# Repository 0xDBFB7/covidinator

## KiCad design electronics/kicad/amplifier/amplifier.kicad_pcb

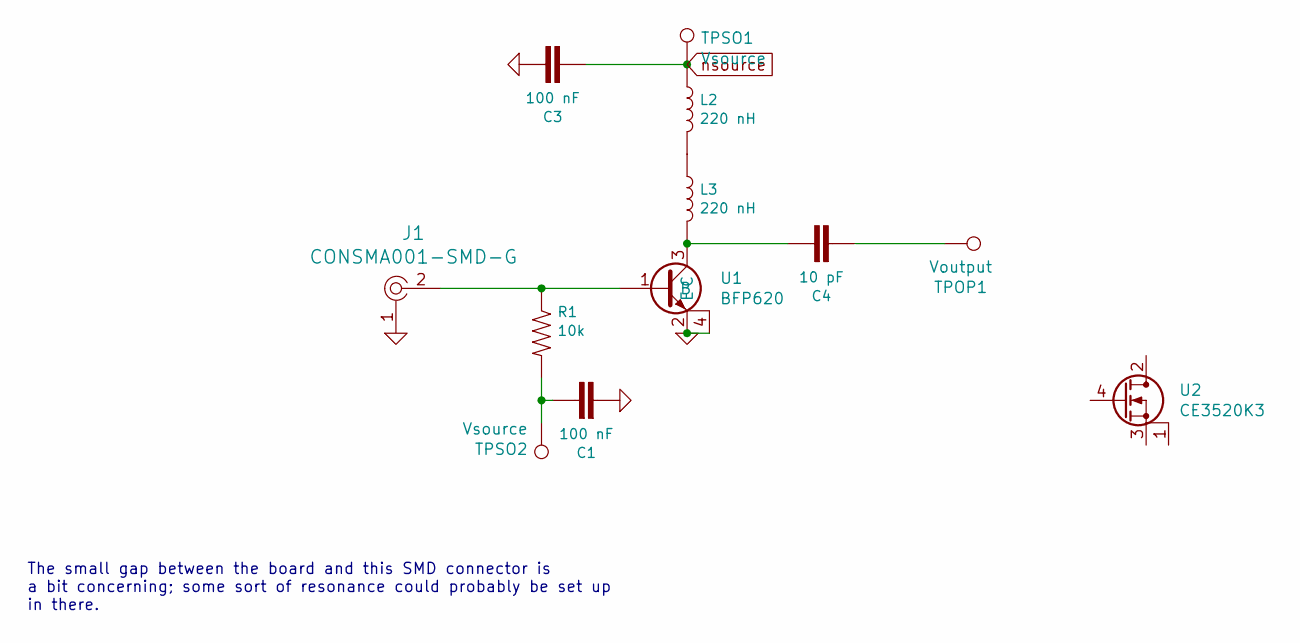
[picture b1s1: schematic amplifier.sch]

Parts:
C1, C3: 100 nF; 0603
C4: 10 pF; C_0402_1005Metric
J1: CONSMA001-SMD-G; RF_SMA_Receptical_Vertical_CONSMA001-SMD-G; MPN CONSMA001-SMD-G; Digi-Key_PN CONSMA001-SMD-G-ND
L2, L3: 220 nH; R_0402_1005Metric
R1: 10k; 0402
TPOP1: Voutput; TestPoint_Pad_1.5x1.5mm
TPSO1, TPSO2: Vsource; TestPoint_Pad_2.0x2.0mm
U1: BFP620; SOT-343_SC-70-4
U2: CE3520K3; 4-Micro-X

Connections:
GND: C1.2, C3.1, J1.1, U1.2 (E), U1.4
unnamed: C1.1, R1.2, TPSO2.1
unnamed: C4.1, L3.2, U1.3 (C)
unnamed: C4.2, TPOP1.1
unnamed: J1.2, R1.1, U1.1 (B)
unnamed: L2.2, L3.1
nsource: C3.2, L2.1, TPSO1.1

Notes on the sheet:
The small gap between the board and this SMD connector is a bit concerning; some sort of resonance could probably be set up in there.

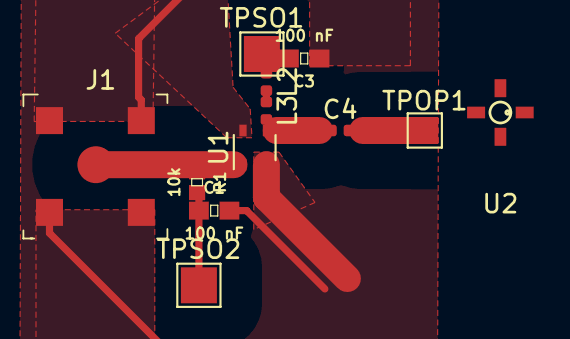
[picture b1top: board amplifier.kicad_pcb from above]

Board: 2 copper layers, 12 parts (0 on the bottom side), 7 nets.

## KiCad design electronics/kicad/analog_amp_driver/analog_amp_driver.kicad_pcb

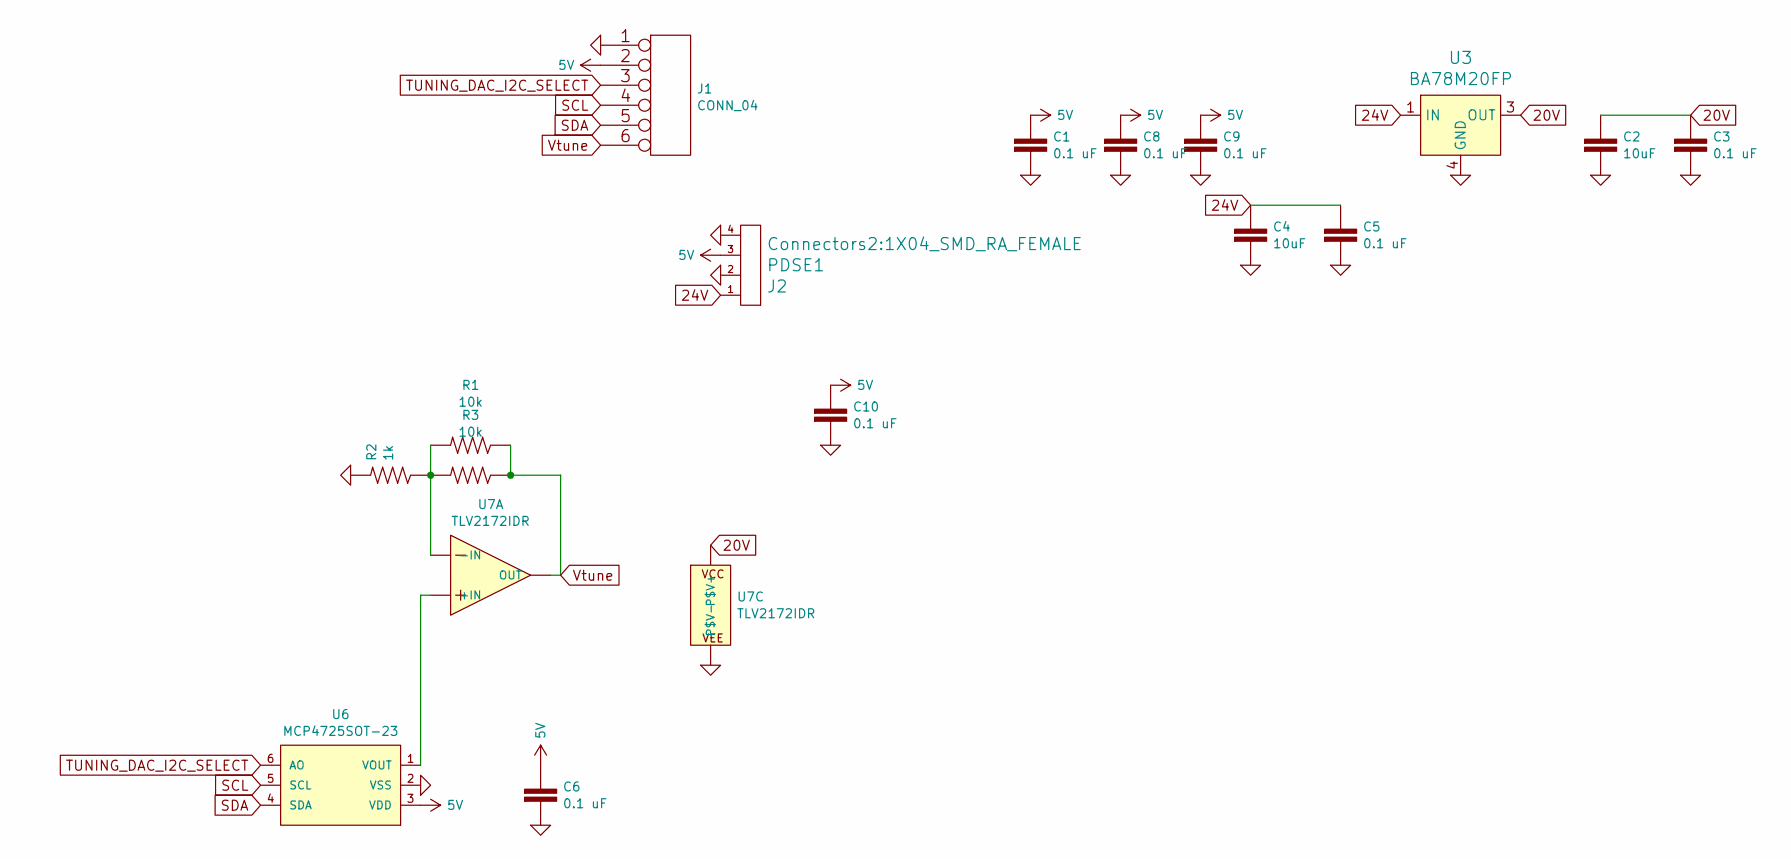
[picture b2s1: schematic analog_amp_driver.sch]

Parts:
C1, C3, C5, C6, C8, C9, C10: 0.1 uF; 0603
C2, C4: 10uF; 1206
J1: CONN_04; 1X06-SMD-FEMALE
J2: PDSE1; 1X04_SMD_RA_FEMALE
R1, R3: 10k; R_0603_1608Metric
R2: 1k; R_0603_1608Metric
U3: BA78M20FP; TO-252-3; MPN MC7805BDTRKG; Digi-Key_PN MC7805BDTRKGOSCT-ND
U6: MCP4725SOT-23; SOT23-6
U7: TLV2172IDR; SOIC-8_3.9x4.9mm_P1.27mm

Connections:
5V: C1.1, C6.1, C8.1, C9.1, C10.1, J1.2, J2.3, U6.3 (VDD)
20V: C2.1, C3.1, U3.3 (OUT), U7.8 (P$V+)
24V: C4.1, C5.1, J2.1, U3.1 (IN)
GND: C1.2, C2.2, C3.2, C4.2, C5.2, C6.2, C8.2, C9.2, C10.2, J1.1, J2.2, J2.4, R2.2, U3.4 (GND), U6.2 (VSS), U7.4 (P$V-)
unnamed: R1.2, R2.1, R3.2, U7.2 (-IN)
unnamed: U6.1 (VOUT), U7.3 (+IN)
SCL: J1.4, U6.5 (SCL)
SDA: J1.5, U6.4 (SDA)
TUNING_DAC_I2C_SELECT: J1.3, U6.6 (AO)
Vtune: J1.6, R1.1, R3.1, U7.1 (OUT)

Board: 2 copper layers, 17 parts (0 on the bottom side), 10 nets, no tracks yet.

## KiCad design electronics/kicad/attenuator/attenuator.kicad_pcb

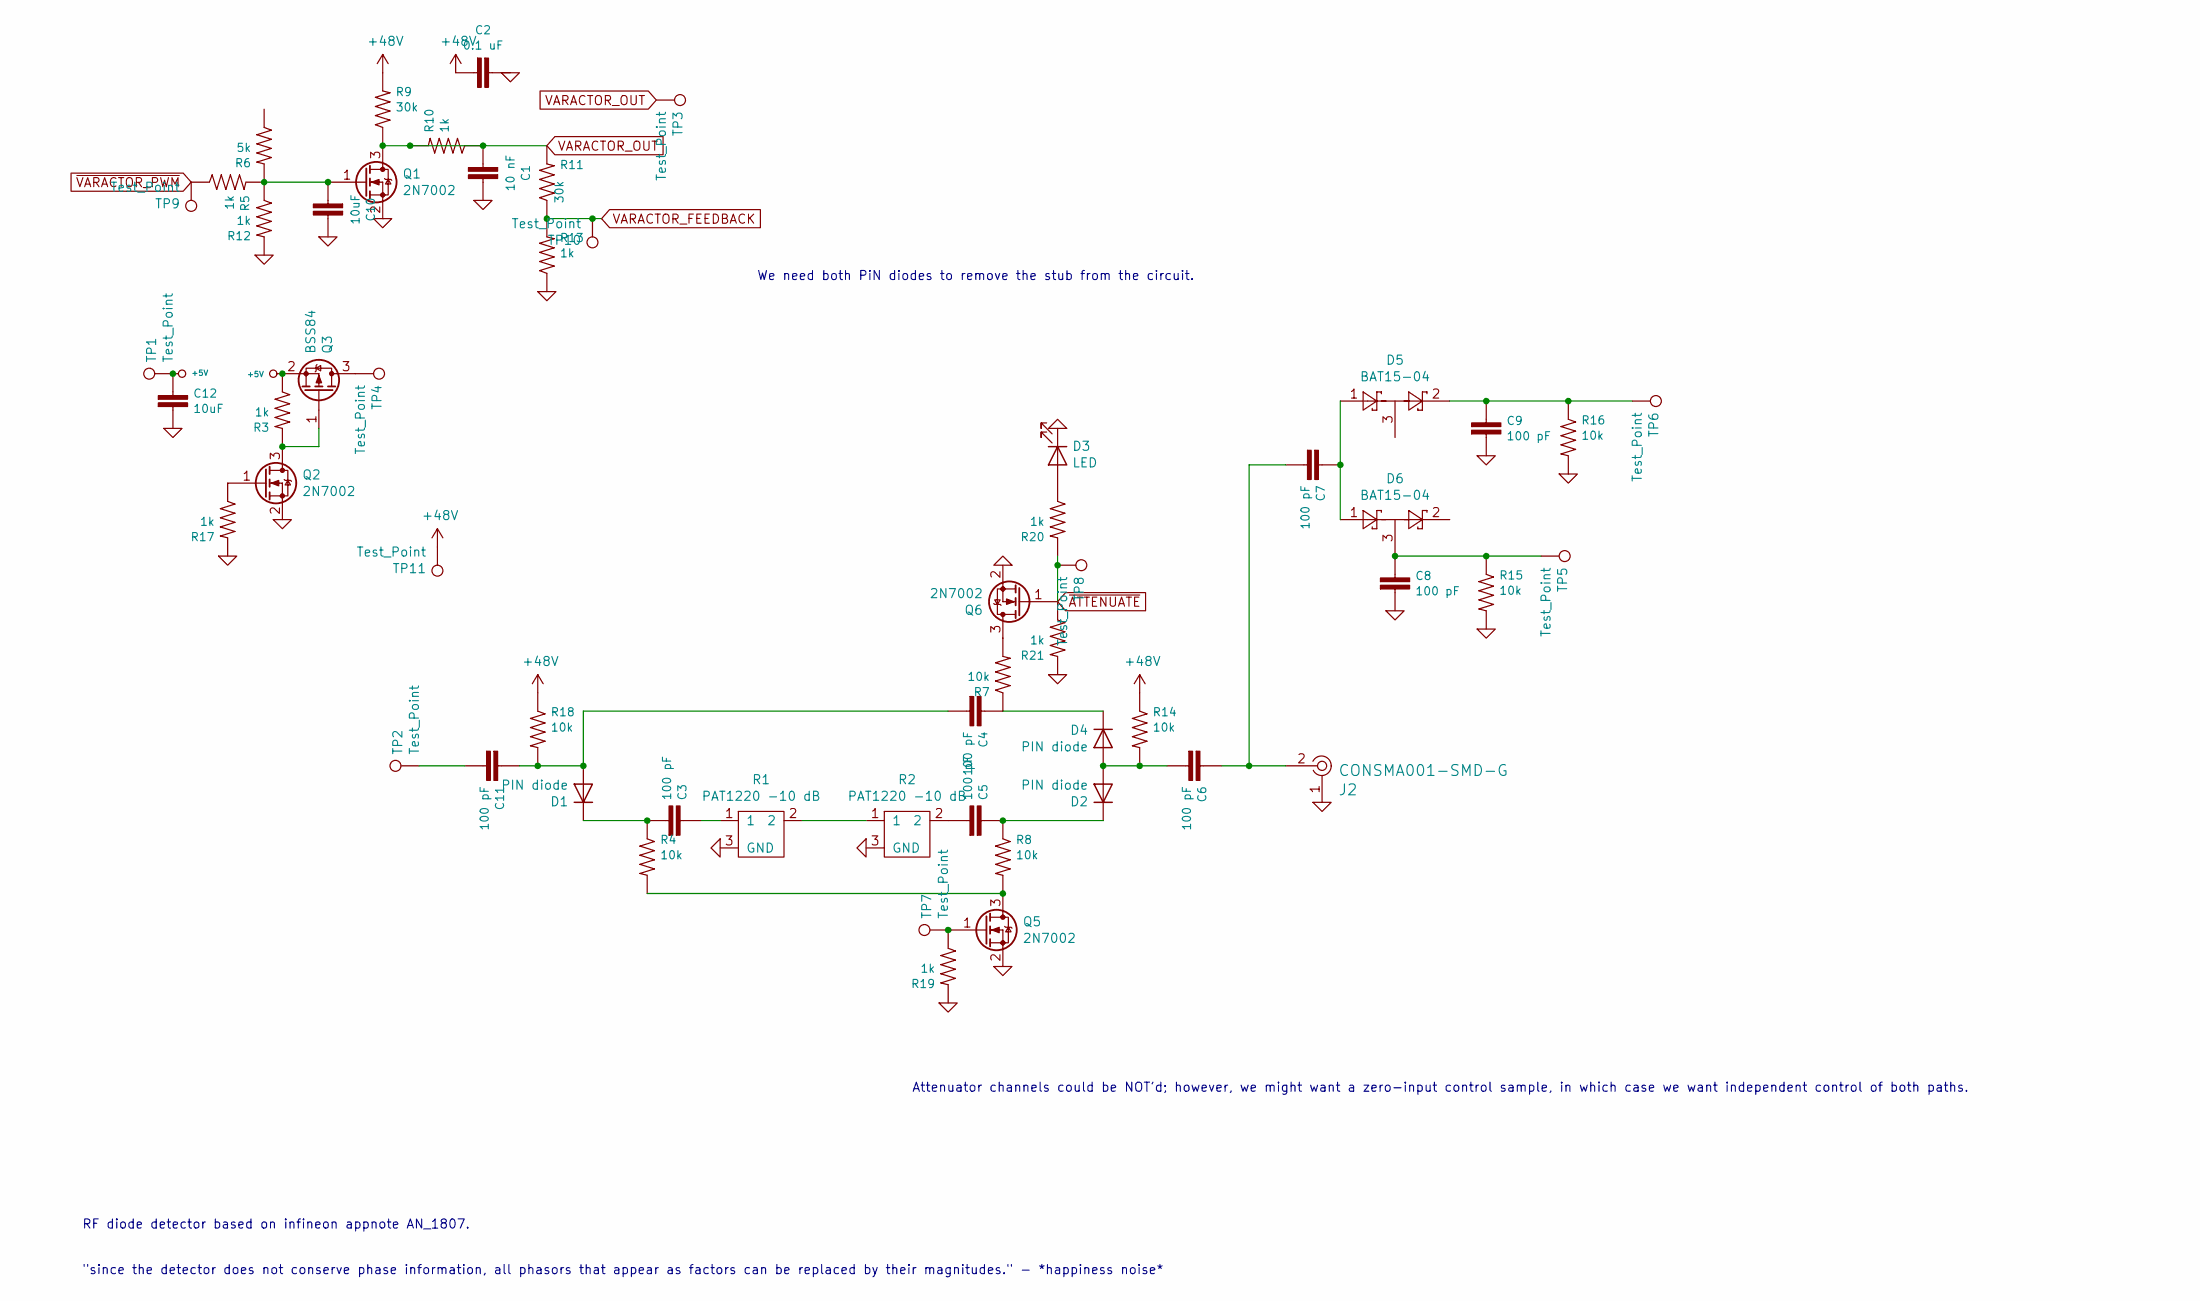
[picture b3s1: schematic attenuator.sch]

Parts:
C1: 10 nF; 0603
C2: 0.1 uF; 0603
C3, C4, C5, C6, C7, C8, C9, C11: 100 pF; 0402
C10: 10uF; 0603
C12: 10uF; 1206
D1, D2, D4: PIN diode; D_SOD-523
D3: LED; LED_0603_1608Metric
D5, D6: BAT15-04; SOT-23
J2: CONSMA001-SMD-G; RF_SMA_Receptical_Vertical_CONSMA001-SMD-G; MPN CONSMA001-SMD-G; Digi-Key_PN CONSMA001-SMD-G-ND
Q1, Q2, Q5, Q6: 2N7002; SOT-23
Q3: BSS84; SOT-23
R1, R2: PAT1220 -10 dB; PAT1220
R3, R5, R10, R12, R13, R17, R19, R20, R21: 1k; R_0603_1608Metric
R4, R7, R8, R14, R15, R16, R18: 10k; 0402
R6: 5k; R_0603_1608Metric
R9, R11: 30k; R_0603_1608Metric
TP1, TP3, TP4, TP5, TP6, TP9, TP10: Test_Point; TestPoint_Pad_2.0x2.0mm
TP2, TP7, TP8, TP11: Test_Point; TestPoint_Pad_1.5x1.5mm

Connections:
+5V: C12.1, Q3.2 (S), R3.1, TP1.1
+48V: C2.2, R9.2, R14.1, R18.1, TP11.1
GND: C1.1, C2.1, C8.2, C9.2, C10.1, C12.2, D3.1 (K), J2.1, Q1.2 (S), Q2.2 (S), Q5.2 (S), Q6.2 (S), R1.3 (GND), R2.3 (GND), R12.2, R13.1, R15.2, R16.2, R17.2, R19.2, R21.2
unnamed: C3.1, R1.1
unnamed: C3.2, D1.1 (K), R4.1
unnamed: C4.1, D4.1 (K), R7.1
unnamed: C5.1, D2.1 (K), R8.1
unnamed: C5.2, R2.2
unnamed: C6.1, C7.2, J2.2
unnamed: C6.2, D2.2 (A), D4.2 (A), R14.2
unnamed: C7.1, D5.1, D6.1
unnamed: C8.1, D6.3, R15.1, TP5.1
unnamed: C9.1, D5.2, R16.1, TP6.1
unnamed: C10.2, Q1.1 (G), R5.2, R6.2, R12.1
unnamed: C4.2, C11.1, D1.2 (A), R18.2
unnamed: C11.2, TP2.1
unnamed: D3.2 (A), R20.1
unnamed: Q2.1 (G), R17.1
unnamed: Q2.3 (D), Q3.1 (G), R3.2
unnamed: Q3.3 (D), TP4.1
unnamed: Q5.1 (G), R19.1, TP7.1
unnamed: Q5.3 (D), R4.2, R8.2
unnamed: Q6.3 (D), R7.2
unnamed: R1.2, R2.1
VARACTOR_FEEDBACK: R11.1, R13.2, TP10.1
VARACTOR_OUT: C1.2, Q1.3 (D), R9.1, R10.1, R10.2, R11.2, TP3.1
~ATTENUATE: Q6.1 (G), R20.2, R21.1, TP8.1
~VARACTOR_PWM: R5.1, TP9.1

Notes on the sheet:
"since the detector does not conserve phase information, all phasors that appear as factors can be replaced by their magnitudes." - *happiness noise*
RF diode detector based on infineon appnote AN_1807.
Attenuator channels could be NOT'd; however, we might want a zero-input control sample, in which case we want independent control of both paths.
We need both PiN diodes to remove the stub from the circuit.

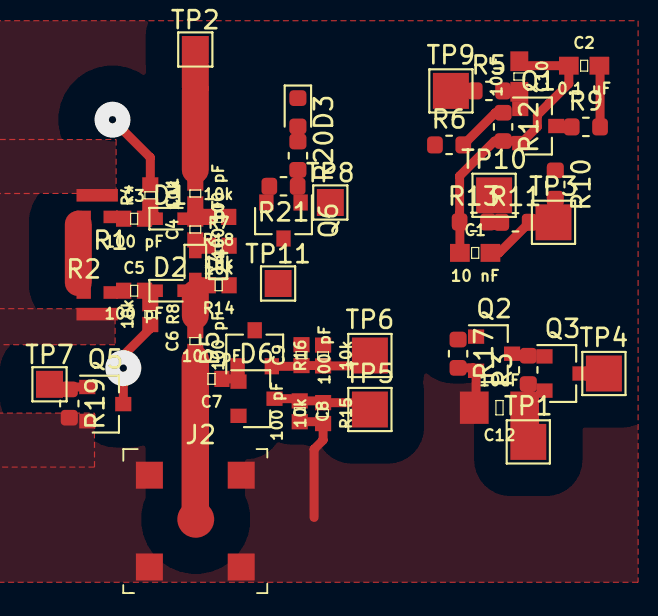
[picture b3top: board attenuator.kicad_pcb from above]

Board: 2 copper layers, 56 parts (0 on the bottom side), 28 nets.

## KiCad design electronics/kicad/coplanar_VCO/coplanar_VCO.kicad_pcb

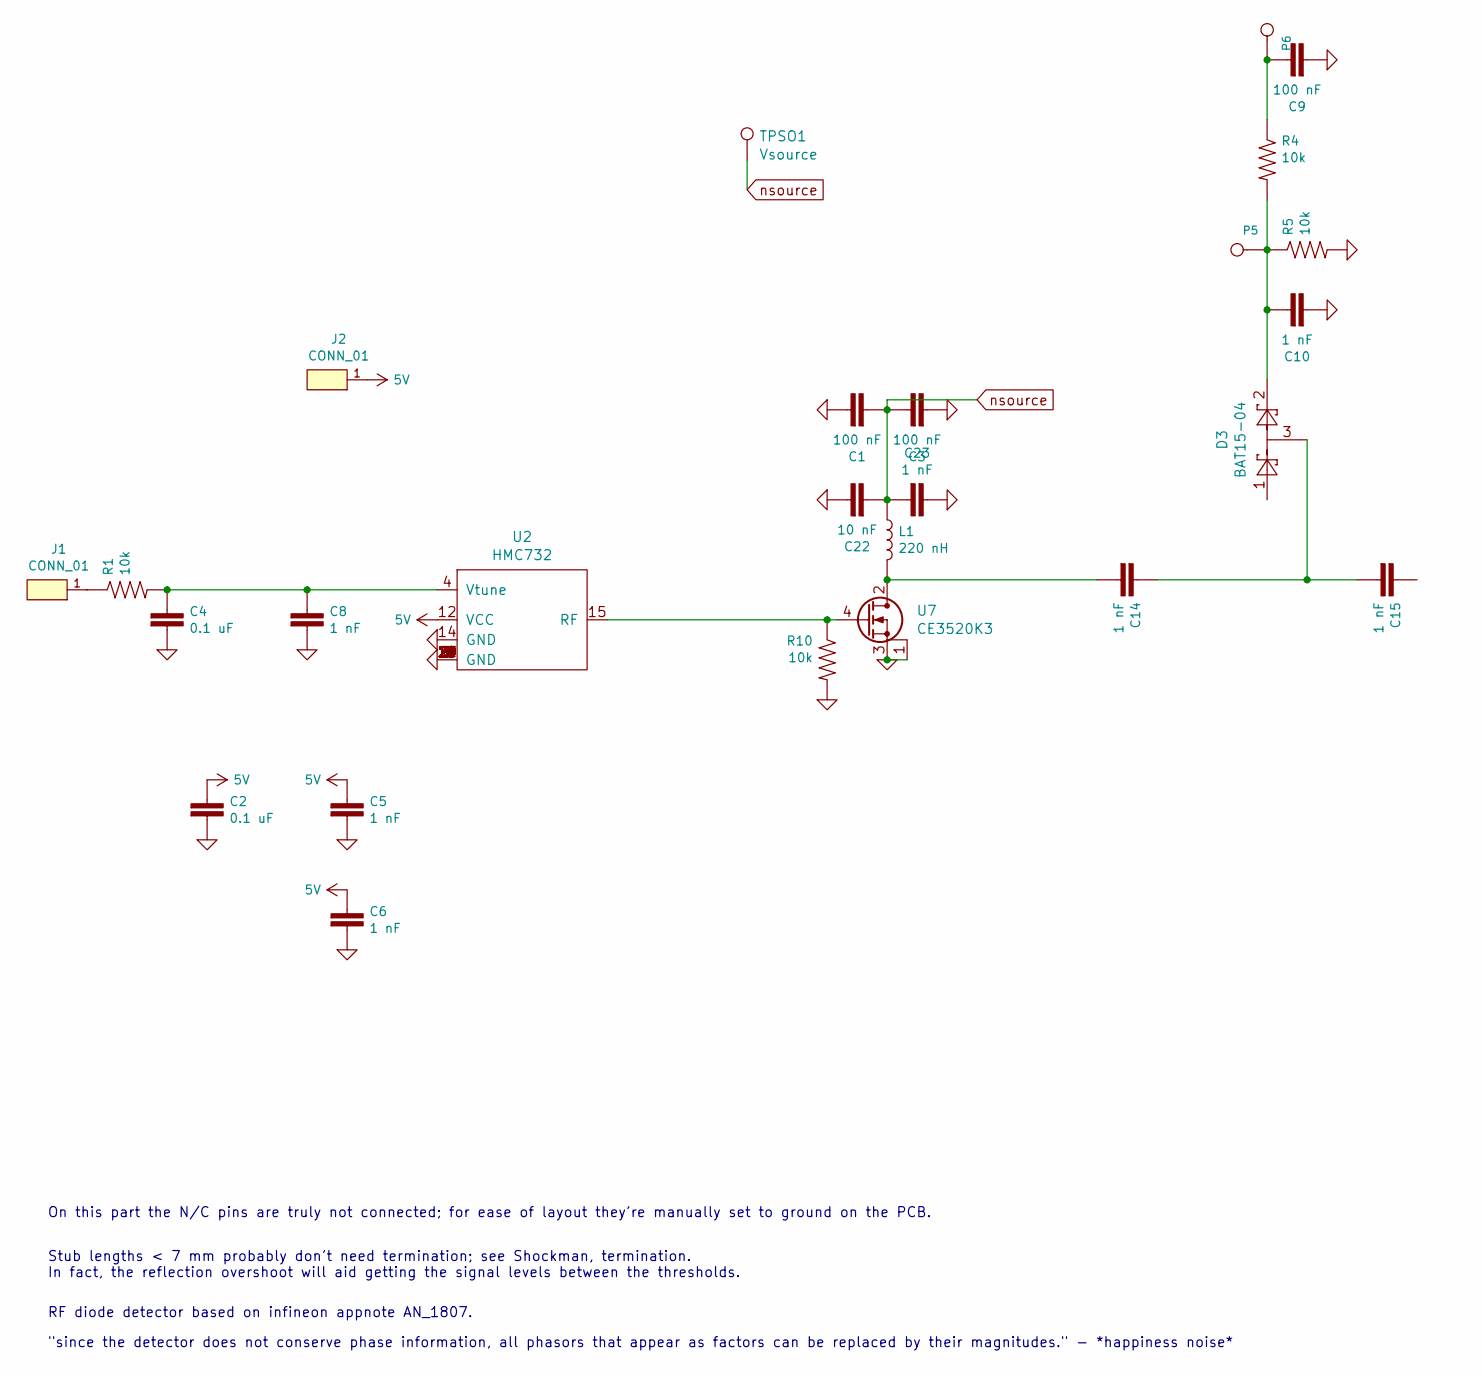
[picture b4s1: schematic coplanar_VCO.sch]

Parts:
C1, C3, C9: 100 nF; 0603
C2, C4: 0.1 uF; 0603
C5, C6, C8: 1 nF; C_0402_1005Metric
C10, C14, C15, C23: 1 nF; R_0402_1005Metric
C22: 10 nF; R_0402_1005Metric
D3: BAT15-04; SOT-23
J1: CONN_01; TestPoint_Pad_2.0x2.0mm
J2: CONN_01; TestPoint_Pad_1.5x1.5mm
L1: 220 nH; R_0402_1005Metric
P5, P6: a; TestPoint_Pad_1.5x1.5mm
R1, R4, R5, R10: 10k; R_0402_1005Metric
TPSO1: Vsource; TestPoint_Pad_2.5x2.5mm
U2: HMC732; QFN-24-1EP_4x4mm_P0.5mm_EP2.6x2.6mm
U7: CE3520K3; 4-Micro-X

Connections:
5V: C2.1, C5.1, C6.1, J2.1, U2.12 (VCC)
GND: C1.1, C2.2, C3.2, C4.2, C5.2, C6.2, C8.2, C9.2, C10.2, C22.1, C23.1, R5.2, R10.2, U2.1 (GND), U2.2 (GND), U2.3 (GND), U2.5 (GND), U2.6 (GND), U2.7 (GND), U2.8 (GND), U2.9 (GND), U2.10 (GND), U2.11 (GND), U2.13 (GND), U2.14 (GND), U2.16 (GND), U2.17 (GND), U2.18 (GND), U2.19 (GND), U2.20 (GND), U2.21 (GND), U2.22 (GND), U2.23 (GND), U2.24 (GND), U2.25 (GND), U7.1, U7.3
unnamed: C4.1, C8.1, R1.2, U2.4 (Vtune)
unnamed: C9.1, P6.1, R4.1
unnamed: C10.1, D3.2, P5.1, R4.2, R5.1
unnamed: C14.1, C15.2, D3.3
unnamed: C14.2, L1.2, U7.2
unnamed: J1.1, R1.1
unnamed: R10.1, U2.15 (RF), U7.4
nsource: C1.2, C3.1, C22.2, C23.2, L1.1, TPSO1.1

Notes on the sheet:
On this part the N/C pins are truly not connected; for ease of layout they're manually set to ground on the PCB.
"since the detector does not conserve phase information, all phasors that appear as factors can be replaced by their magnitudes." - *happiness noise*
RF diode detector based on infineon appnote AN_1807.
Stub lengths < 7 mm probably don't need termination; see Shockman, termination. In fact, the reflection overshoot will aid getting the signal levels between the thresholds.

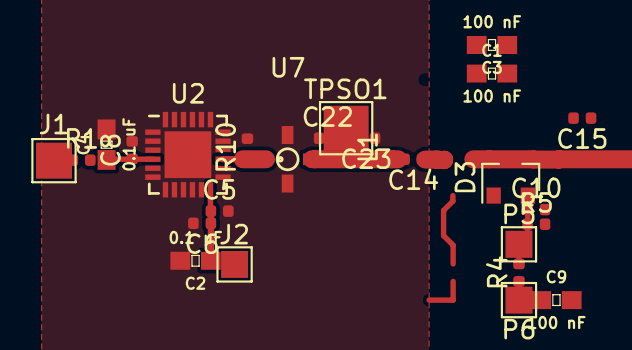
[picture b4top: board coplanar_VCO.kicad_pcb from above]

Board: 2 copper layers, 26 parts (0 on the bottom side), 10 nets.

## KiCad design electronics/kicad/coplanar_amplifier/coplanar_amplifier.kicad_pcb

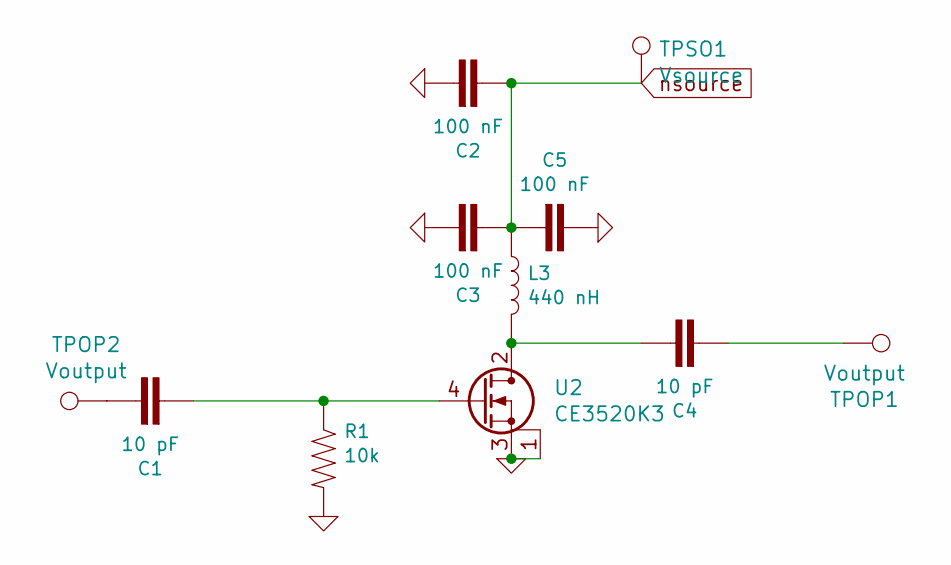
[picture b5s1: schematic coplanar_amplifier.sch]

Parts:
C1, C4: 10 pF; C_0402_1005Metric
C2: 100 nF; 0603
C3, C5: 100 nF; R_0402_1005Metric
L3: 440 nH; R_0402_1005Metric
R1: 10k; R_0402_1005Metric
TPOP1, TPOP2: Voutput; TestPoint_Pad_1.0x1.0mm
TPSO1: Vsource; TestPoint_Pad_1.0x1.0mm
U2: CE3520K3; 4-Micro-X

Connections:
GND: C2.1, C3.1, C5.1, R1.2, U2.1, U2.3
unnamed: C1.1, TPOP2.1
unnamed: C1.2, R1.1, U2.4
unnamed: C4.1, L3.2, U2.2
unnamed: C4.2, TPOP1.1
nsource: C2.2, C3.2, C5.2, L3.1, TPSO1.1

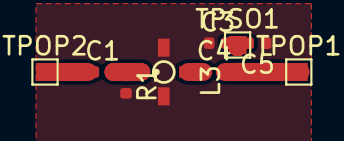
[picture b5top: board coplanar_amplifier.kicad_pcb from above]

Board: 2 copper layers, 10 parts (0 on the bottom side), 6 nets.

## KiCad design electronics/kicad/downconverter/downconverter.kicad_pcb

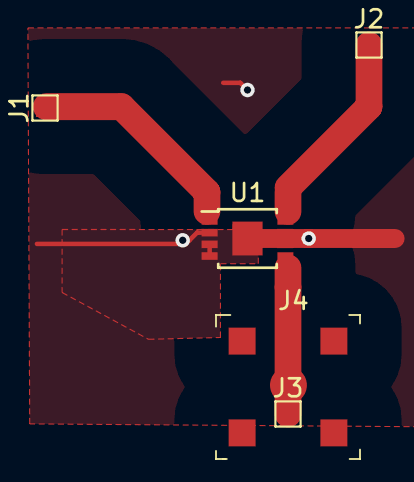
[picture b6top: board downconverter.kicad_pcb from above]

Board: 2 copper layers, 5 parts (0 on the bottom side), 4 nets.

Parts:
J1, J2, J3: CONN_01; TestPoint_Pad_1.0x1.0mm
J4: CONSMA001-SMD-G; RF_SMA_Receptical_Vertical_CONSMA001-SMD-G
U1: HMC220B; MSOP-8-1EP_3x3mm_P0.65mm_EP1.68x1.88mm

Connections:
GND: U1.2, U1.3, U1.4, U1.6, U1.7, U1.9
unnamed: J1.1, U1.1
unnamed: J2.1, U1.8
unnamed: J3.1, U1.5
